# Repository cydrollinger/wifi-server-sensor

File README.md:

<a href="https://elec-real.com/case-studies/wifi-server-sensor/"></img></a>

>Electronic Realization L.L.C.								   
>Design: Wifi communication web server 		   
>Engineer: Cy Drollinger								   
>Date: 8/15												           
>Email: cy@elec-real.com
>Website: https://elec-real.com								   
>Address: 2023 Stadium Dr Suite 2B #210 Bozeman, MT 59715				   
>Phone: 406-539-8117	

**NOTE:**
 This design has been tested and functions as specified. The design is provided gratis, so, please 
 think critically while utilizing and or redesigning. Open electronic circuitry can be dangerous due 
 to easily shorting circuits which can generate immediate and intense heat resulting in fire. Conversation is
 welcome to improve this design and repository, but, be advised ER is a professional design house and
 monetary compensation is required for additional work toward this design enabling your success.			   

**PURPOSE:**
This is a redesign of a Microchip product, a web server. 

>**File Arcitecture with a terse description**

* FOLDERS:
	* docs		: datasheets 
	* hardware	: eagle cadsoft(v7.7) hardware design files 	
		* eagleup		: 3D files 
		* library		: eagle part files 
		* manufacturing	: files required to produce the design
			* bom	: files created to order the parts	
			* gerber	: files generated to manufacture the board
				* <a href="https://oshpark.com/shared_projects/WaZovepw"></img></a>
			* mount	: 
			
	* firmware
	* flexware
	* software

	* readme.md	: this file

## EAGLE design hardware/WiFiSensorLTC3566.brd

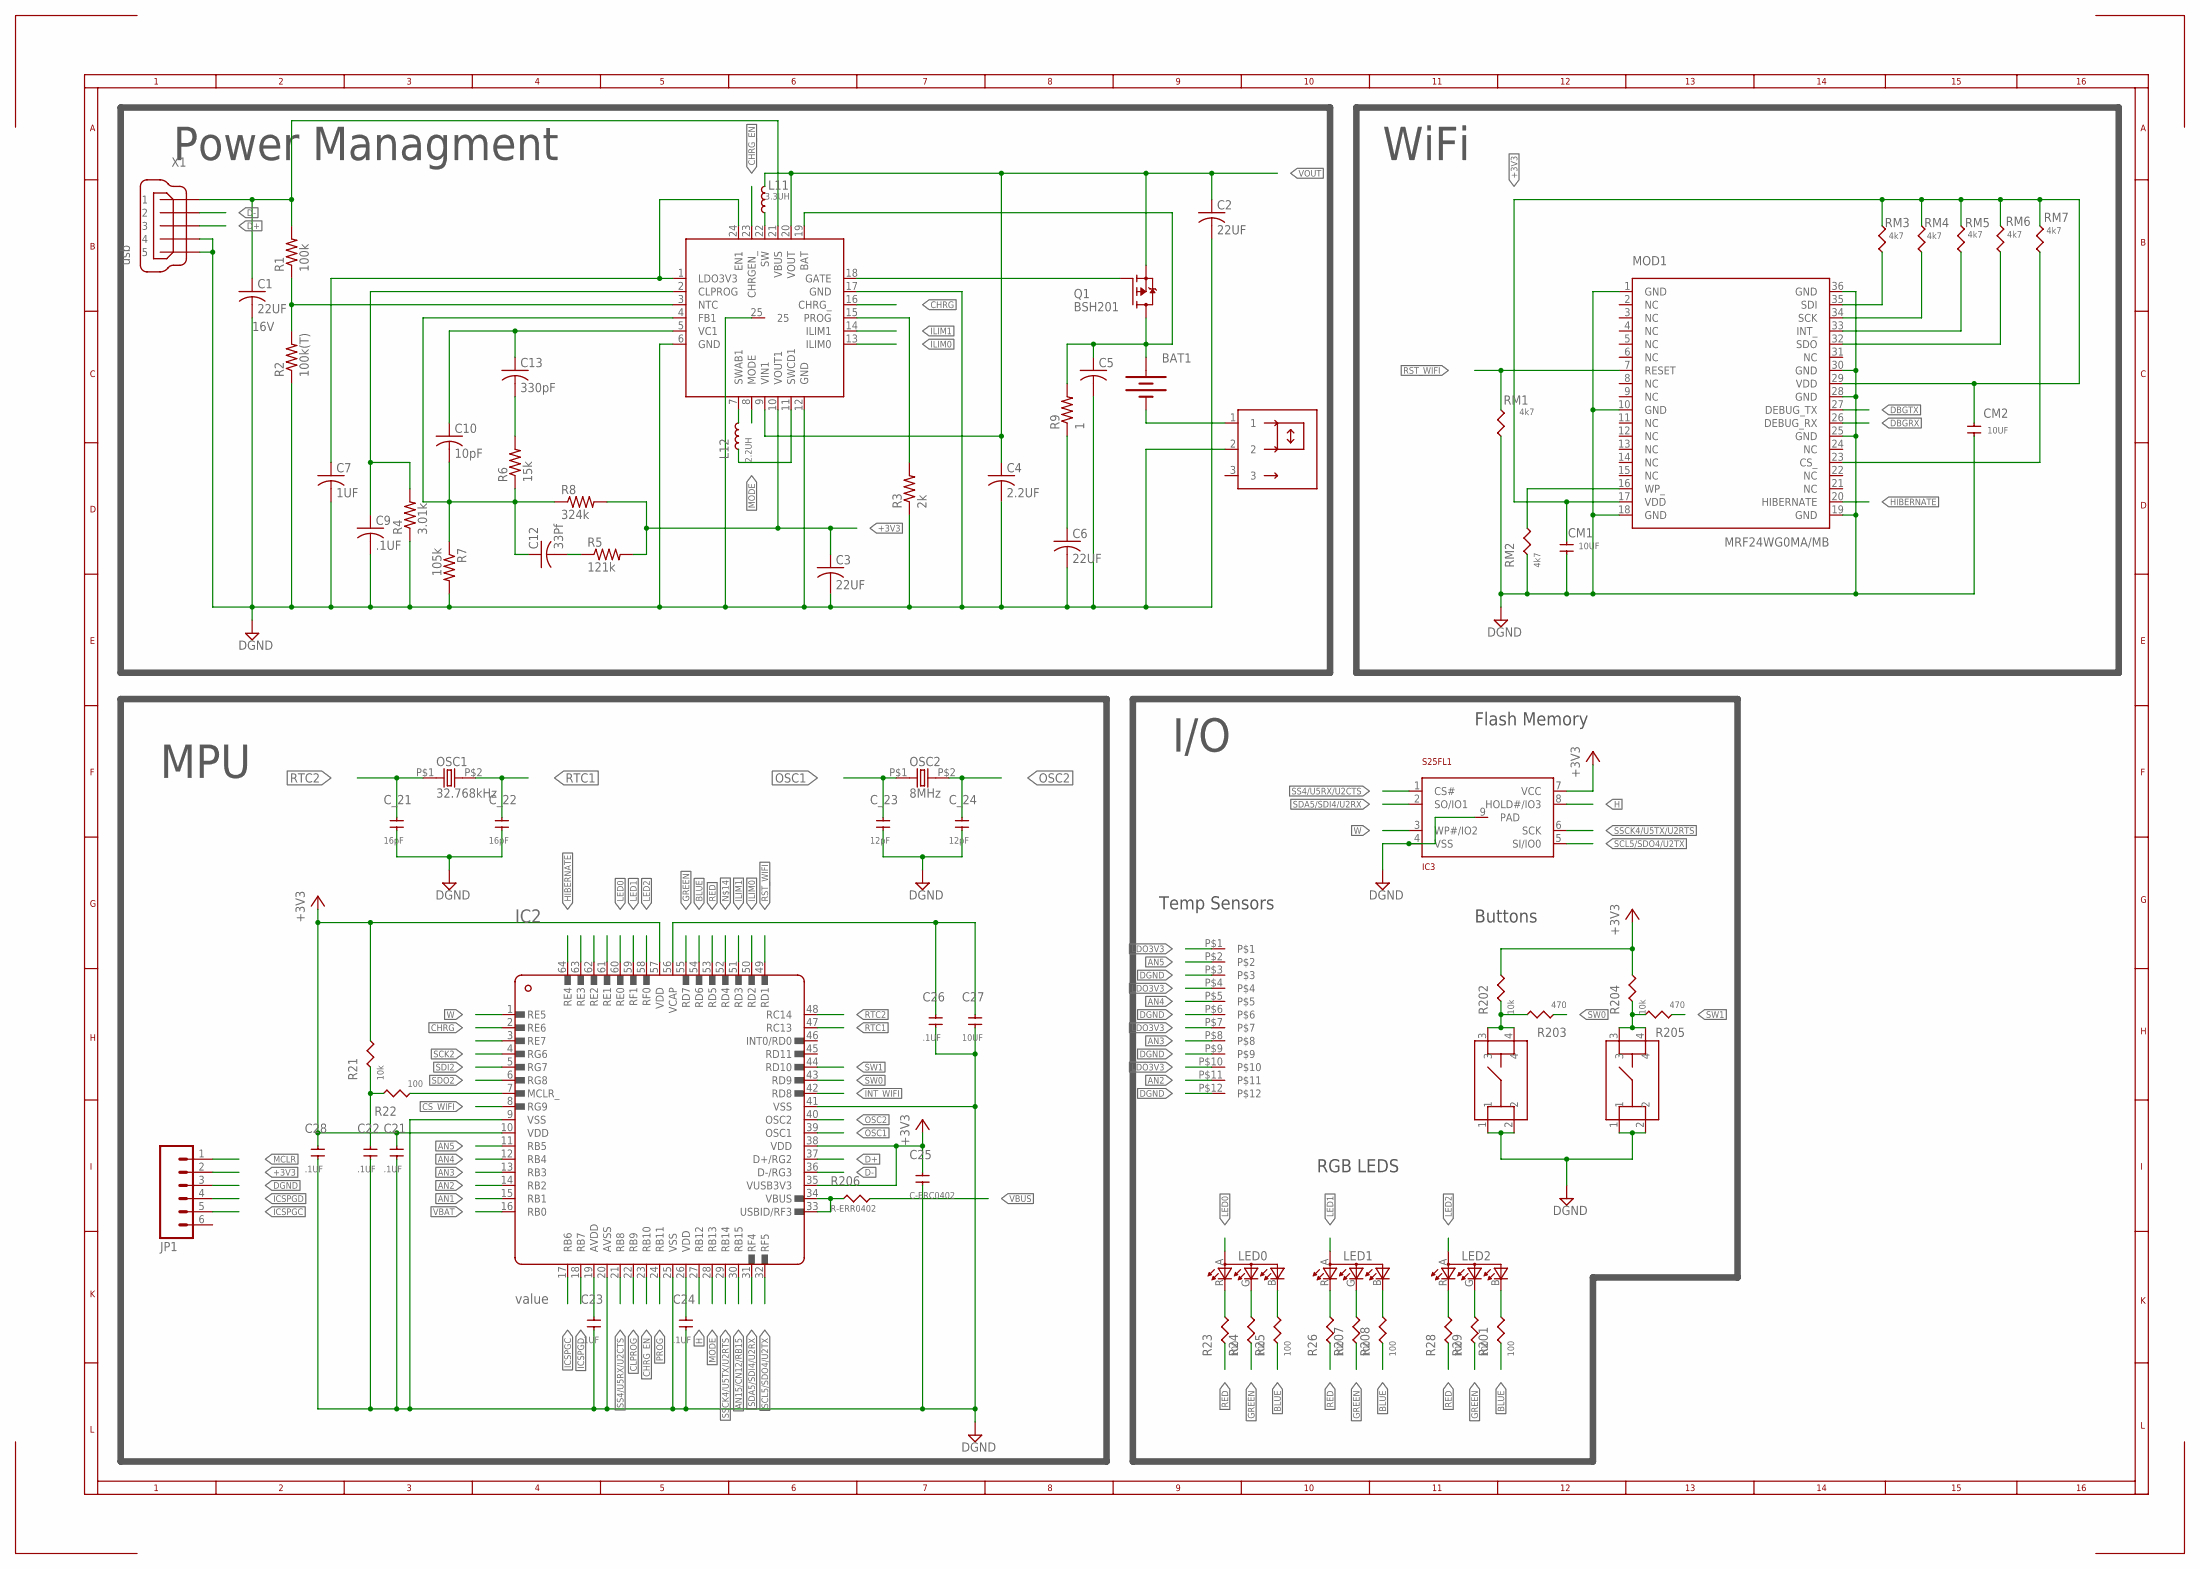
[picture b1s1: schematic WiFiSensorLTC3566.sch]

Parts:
BAT1: BATTERY245PTH; BATTCON_245MM_PTH
C1: 22UF; C0805; VOLTAGECOEFFECIENT 16V
C2, C3, C6: 22UF; C0805
C4: 2.2UF; C0805
C5: C-USC0402; C0402
C7: 1UF; C0805
C9, C21, C22, C23, C24, C26, C28: .1UF; C0402
C10: 10pF; C0402
C12: 33Pf; C0402
C13: 330pF; C0402
C25: C-ERC0402; C0402
C27: 10UF; C0805
CM1, CM2: 10UF; C0805
C_21, C_22: 16pF; C0402
C_23, C_24: 12pF; C0402
IC1: LTC3566-2; QFN24-4X4
IC2: PICMX32695F512H; TQFP64
IC3: S25FL1; 8WSON
JP1: M06LOCK; 1X06_LOCK
JP2: 12_127; 12-127
L11: 3.3UH; VLCF5020
L12: 2.2UH; VLCF5020
LED0, LED1, LED2: 1X1RGB; 1X1
MOD1: MRF24WG0MA/MB; MRF24
OSC1: 32.768kHz; ECX39; DIGIPART XC1658CT-ND
OSC2: 8MHz; CX532; DIGIPART XC1658CT-ND
Q1: BSH201; SOT23
R1: 100k; R0402
R2: 100k(T); R0402
R3: 2k; R0402
R4: 3.01k; R0402
R5: 121k; R0402
R6: 15k; R0402
R7: 105k; R0402
R8: 324k; R0402
R9: 1; R0402
R21, R202, R204: 10k; R0402
R22, R23, R24, R25, R26, R28, R29, R201, R207, R208: 100; R0402
R203, R205: 470; R0402
R206: R-ERR0402; R0402
RM1, RM2, RM3, RM4, RM5, RM6, RM7: 4k7; R0402
SW0, SW1: ADTS; 4X5
SW2: C&K_JS; SAQN
X1: usb; UX60A-MB-5ST

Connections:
+3V3: C3.1, C21.2, C24.2, C25.2, C28.2, CM1.2, CM2.2, IC1.10 (VOUT1), IC2.10 (VDD), IC2.26 (VDD), IC2.35 (VUSB3V3), IC2.38 (VDD), IC2.57 (VDD), IC3.7 (VCC), JP1.2, MOD1.17 (VDD), MOD1.29 (VDD), R5.2, R8.2, R21.2, R202.2, R204.2, RM3.2, RM4.2, RM5.2, RM6.2, RM7.2
AN1: IC2.15 (RB1)
AN2: IC2.14 (RB2), JP2.P$11
AN3: IC2.13 (RB3), JP2.P$8
AN4: IC2.12 (RB4), JP2.P$5
AN5: IC2.11 (RB5), JP2.P$2
AN15/CN12/RB15: IC2.30 (RB15)
BLUE: IC2.54 (RD6), R25.1, R201.1, R208.1
CHRG: IC1.16 (CHRG_), IC2.2 (RE6)
CHRG_EN: IC1.23 (CHRGEN_), IC2.23 (RB10)
CLPROG: C9.1, IC1.2 (CLPROG), IC2.22 (RB9), R4.2
CS_WIFI: IC2.8 (RG9), MOD1.23 (CS_), RM7.1
D+: IC2.37 (D+/RG2), X1.3
D-: IC2.36 (D-/RG3), X1.2
DBGRX: MOD1.26 (DEBUG_RX)
DBGTX: MOD1.27 (DEBUG_TX)
DGND: C1.2, C2.2, C3.2, C4.2, C5.2, C6.2, C7.2, C9.2, C21.1, C22.1, C23.1, C24.1, C25.1, C26.1, C27.1, C28.1, CM1.1, CM2.1, C_21.1, C_22.1, C_23.1, C_24.1, IC1.6 (GND), IC1.12 (GND), IC1.17 (GND), IC1.25, IC2.9 (VSS), IC2.20 (AVSS), IC2.25 (VSS), IC2.41 (VSS), IC3.4 (VSS), IC3.9 (PAD), JP1.3, JP2.P$3, JP2.P$6, JP2.P$9, JP2.P$12, MOD1.1 (GND), MOD1.10 (GND), MOD1.18 (GND), MOD1.19 (GND), MOD1.25 (GND), MOD1.28 (GND), MOD1.30 (GND), MOD1.36 (GND), R2.1, R3.1, R4.1, R7.2, RM1.1, RM2.1, SW0.1, SW0.2, SW1.1, SW1.2, SW2.2, X1.4, X1.5
GREEN: IC2.55 (RD7), R24.1, R29.1, R207.1
H: IC2.27 (RB12), IC3.8 (HOLD#/IO3)
HIBERNATE: IC2.64 (RE4), MOD1.20 (HIBERNATE)
ICSPGC: IC2.17 (RB6), JP1.5
ICSPGD: IC2.18 (RB7), JP1.4
ILIM0: IC1.13 (ILIM0), IC2.50 (RD2)
ILIM1: IC1.14 (ILIM1), IC2.51 (RD3)
INT_WIFI: IC2.42 (RD8), MOD1.33 (INT_), RM5.1
LDO3V3: C7.1, C23.2, IC1.1 (LDO3V3), IC1.24 (EN1), IC2.19 (AVDD), JP2.P$1, JP2.P$4, JP2.P$7, JP2.P$10
LED0: IC2.60 (RE0), LED0.A (A2)
LED1: IC2.59 (RF1), LED1.A (A2)
LED2: IC2.58 (RF0), LED2.A (A2)
MCLR: C22.2, JP1.1, R21.1, R22.2
MODE: IC1.8 (MODE), IC2.28 (RB13)
unnamed: IC1.22 (SW), L11.P$1
unnamed: C6.1, R9.1
unnamed: IC1.7 (SWAB1), L12.P$2
unnamed: IC1.11 (SWCD1), L12.P$1
unnamed: C12.2, R5.1
unnamed: IC1.3 (NTC), R1.1, R2.2
unnamed: C13.2, R6.2
unnamed: C10.1, C13.1, IC1.5 (VC1)
unnamed: C10.2, C12.1, IC1.4 (FB1), R6.1, R7.1, R8.1
unnamed: BAT1.2 (-), SW2.1
unnamed: IC1.18 (GATE), Q1.1 (G)
unnamed: IC2.33 (USBID/RF3), IC2.34 (VBUS), R206.1
unnamed: IC2.7 (MCLR_), R22.1
unnamed: R202.1, R203.2, SW0.3, SW0.4
unnamed: C26.2, C27.2, IC2.56 (VCAP)
unnamed: R204.1, R205.2, SW1.3, SW1.4
unnamed: LED0.R (CRED), R23.2
unnamed: LED0.G (CBLUE), R24.2
unnamed: MOD1.16 (WP_), RM2.2
unnamed: LED0.B (CGREEN), R25.2
unnamed: LED1.R (CRED), R26.2
unnamed: LED1.G (CBLUE), R207.2
unnamed: LED1.B (CGREEN), R208.2
unnamed: LED2.R (CRED), R28.2
unnamed: LED2.G (CBLUE), R29.2
unnamed: LED2.B (CGREEN), R201.2
OSC1: C_23.2, IC2.39 (OSC1), OSC2.P$1 (1)
OSC2: C_24.2, IC2.40 (OSC2), OSC2.P$2 (2)
PROG: IC1.15 (PROG), IC2.24 (RB11), R3.2
RED: IC2.53 (RD5), R23.1, R26.1, R28.1
RST_WIFI: IC2.49 (RD1), MOD1.7 (RESET), RM1.2
RTC1: C_22.2, IC2.47 (RC13), OSC1.P$2 (2)
RTC2: C_21.2, IC2.48 (RC14), OSC1.P$1 (1)
SCK2: IC2.4 (RG6), MOD1.34 (SCK), RM4.1
SCL5/SDO4/U2TX: IC2.32 (RF5), IC3.5 (SI/IO0)
SDA5/SDI4/U2RX: IC2.31 (RF4), IC3.2 (SO/IO1)
SDI2: IC2.5 (RG7), MOD1.32 (SDO), RM6.1
SDO2: IC2.6 (RG8), MOD1.35 (SDI), RM3.1
SS4/U5RX/U2CTS: IC2.21 (RB8), IC3.1 (CS#)
SSCK4/U5TX/U2RTS: IC2.29 (RB14), IC3.6 (SCK)
SW0: IC2.43 (RD9), R203.1
SW1: IC2.44 (RD10), R205.1
VBAT: BAT1.3 (+), C5.1, IC1.19 (BAT), IC2.16 (RB0), Q1.3 (D), R9.2
VBUS: C1.1, IC1.21 (VBUS), R1.2, R206.2, X1.1
VOUT: C2.1, C4.1, IC1.9 (VIN1), IC1.20 (VOUT), L11.P$2, Q1.2 (S)
W: IC2.1 (RE5), IC3.3 (WP#/IO2)

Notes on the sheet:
WiFi
Power Managment
MPU
I/O
Temp Sensors
Buttons
RGB LEDS
Flash Memory

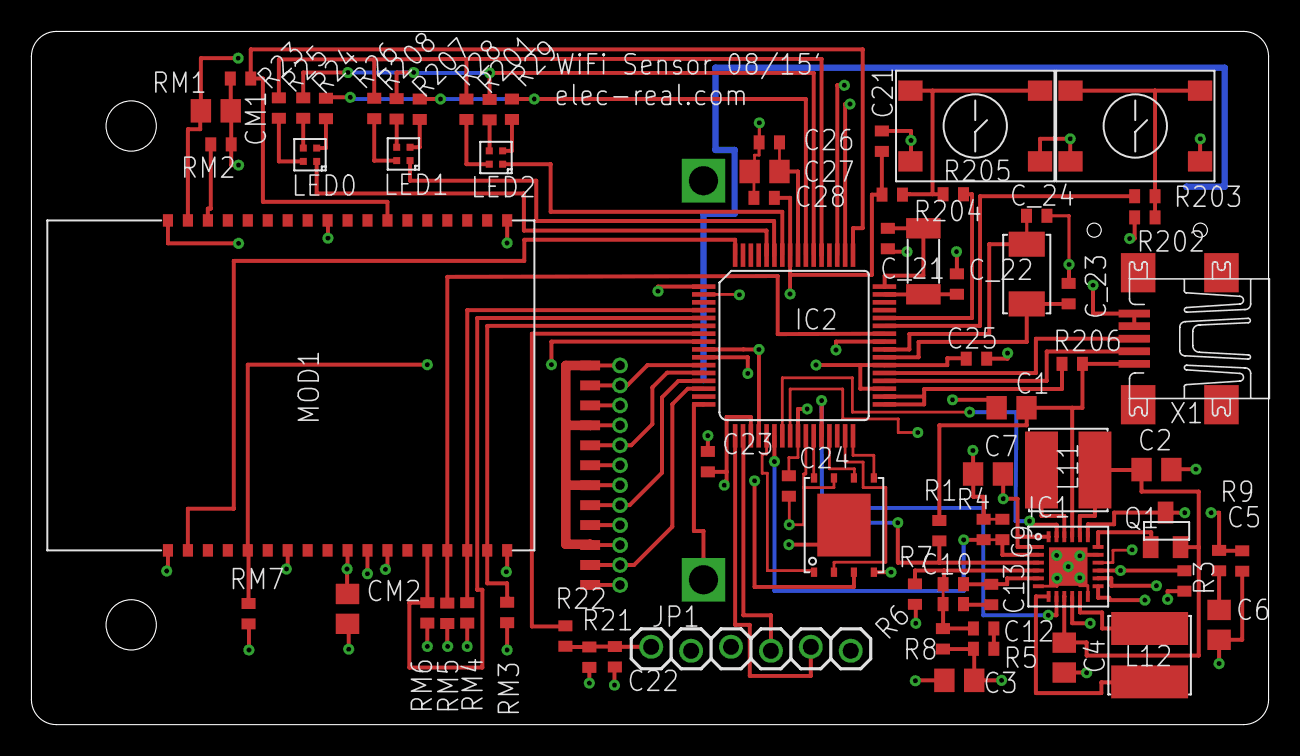
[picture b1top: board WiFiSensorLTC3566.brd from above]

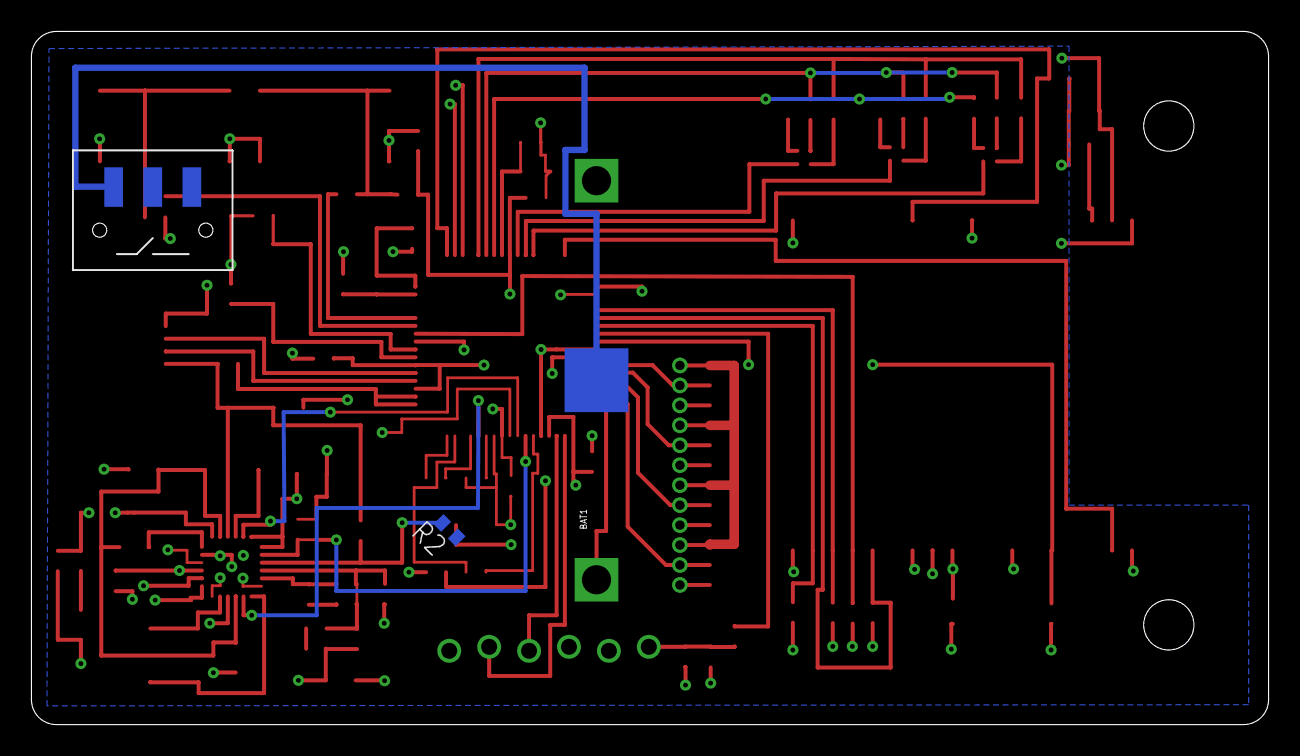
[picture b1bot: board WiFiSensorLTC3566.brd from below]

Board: 4 copper layers, 78.7 x 44.1 mm, 76 parts (3 on the bottom side), 73 nets.

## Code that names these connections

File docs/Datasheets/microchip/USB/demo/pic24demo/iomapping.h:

/************************************************************************
*                                                                       *
* This redefines I/O mapping for each device family                     *
*                                                                       *
*************************************************************************
* Company:             Microchip Technology, Inc.                       *
*                                                                       *
* Software License Agreement                                            *
*                                                                       *
* The software supplied herewith by Microchip Technology Incorporated   *
* (the "Company") for its PICmicro® Microcontroller is intended and     *
* supplied to you, the Company's customer, for use solely and           *
* exclusively on Microchip PICmicro Microcontroller products. The       *
* software is owned by the Company and/or its supplier, and is          *
* protected under applicable copyright laws. All rights are reserved.   *
* Any use in violation of the foregoing restrictions may subject the    *
* user to criminal sanctions under applicable laws, as well as to       *
* civil liability for the breach of the terms and conditions of this    *
* license.                                                              *
*                                                                       *
* THIS SOFTWARE IS PROVIDED IN AN "AS IS" CONDITION. NO WARRANTIES,     *
* WHETHER EXPRESS, IMPLIED OR STATUTORY, INCLUDING, BUT NOT LIMITED     *
* TO, IMPLIED WARRANTIES OF MERCHANTABILITY AND FITNESS FOR A           *
* PARTICULAR PURPOSE APPLY TO THIS SOFTWARE. THE COMPANY SHALL NOT,     *
* IN ANY CIRCUMSTANCES, BE LIABLE FOR SPECIAL, INCIDENTAL OR            *
* CONSEQUENTIAL DAMAGES, FOR ANY REASON WHATSOEVER.                     *
************************************************************************/

#ifndef IOMAPPING_H	
#define IOMAPPING_H

extern void ioMap();
extern void unlock();
extern void lockIO();

    #if defined(__PIC24FJ64GA004__)
        //ADC input mapping
        #define AN_VOLT_PIN  	AD1PCFGbits.PCFG7			//voltage input on AN7
        #define ADC_VOLT_CHAN	7
        
        #define AN_TEMP_PIN	 	AD1PCFGbits.PCFG6 			//temp input on AN6
        #define ADC_TEMP_CHAN	6
                
        //Push Button I/O Mapping
        #define BUTTON1_IO		PORTAbits.RA10
        #define BUTTON2_IO		PORTAbits.RA9
        #define BUTTON3_IO		PORTCbits.RC6
        #define BUTTON4_IO		PORTAbits.RA7
        
        #define BUTTON1_TRIS	TRISAbits.TRISA10
        #define BUTTON2_TRIS	TRISAbits.TRISA9
        #define BUTTON3_TRIS	TRISCbits.TRISC6
        #define BUTTON4_TRIS	TRISAbits.TRISA7
        
        
        //LED I/O Mapping
        #define LED0_IO			LATAbits.LATA10
        #define LED1_IO			LATAbits.LATA7
        #define LED2_IO			LATBbits.LATB8
        #define LED3_IO			LATBbits.LATB9
        #define LED4_IO			LATAbits.LATA9
        #define LED5_IO			LATAbits.LATA8
        #define LED6_IO			LATBbits.LATB12
        #define LED7_IO			LATCbits.LATC6
        
        #define LED0_TRIS		TRISAbits.TRISA10
        #define LED1_TRIS		TRISAbits.TRISA7			
        #define LED2_TRIS		TRISBbits.TRISB8
        #define LED3_TRIS		TRISBbits.TRISB9
        #define LED4_TRIS		TRISAbits.TRISA9
        #define LED5_TRIS		TRISAbits.TRISA8
        #define LED6_TRIS		TRISBbits.TRISB12
        #define LED7_TRIS		TRISCbits.TRISC6
        
        
        //SPI I/O Mapping
        #define PPS_SPI_SS_IO		LATAbits.LATA8
        #define PPS_SPI_SS_TRIS	    TRISAbits.TRISA8
        #define PPS_SPI_SCK_TRIS	TRISCbits.TRISC8
        #define PPS_SPI_SDI_TRIS	TRISCbits.TRISC4
        #define PPS_SPI_SDO_TRIS	TRISCbits.TRISC5
        
        
        //UART I/O Mapping
        #define PPS_UART2_TX_TRIS		TRISCbits.TRISC9
        #define PPS_UART2_RX_TRIS		TRISCbits.TRISC3
        
        //PPS Outputs
        #define NULL_IO		0
        #define C1OUT_IO	1
        #define C2OUT_IO	2
        #define U1TX_IO		3
        #define U1RTS_IO	4
        #define U2TX_IO		5
        #define U2RTS_IO	6
        #define SDO1_IO		7
        #define SCK1OUT_IO	8
        #define SS1OUT_IO	9
        #define SDO2_IO		10
        #define SCK2OUT_IO	11
        #define SS2OUT_IO	12
        #define OC1_IO		18
        #define OC2_IO		19
        #define OC3_IO		20
        #define OC4_IO		21
        #define OC5_IO		22
    #endif //__PIC24FJ64GA004__

    #if defined(__PIC24FJ256GB110__) || defined(__PIC24FJ256GA110__)
        //ADC input mapping
        #define AN_VOLT_PIN  	AD1PCFGbits.PCFG5			//voltage input on AN5
        #define ADC_VOLT_CHAN	5
        
        #define AN_TEMP_PIN	 	AD1PCFGbits.PCFG4 			//temp input on AN4
        #define ADC_TEMP_CHAN	4
        
        
        //Push Button I/O Mapping
        #define BUTTON1_IO		PORTDbits.RD6
        #define BUTTON2_IO		PORTDbits.RD7
        #define BUTTON3_IO		PORTAbits.RA7
        #define BUTTON4_IO		PORTDbits.RD13
        
        #define BUTTON1_TRIS	TRISDbits.TRISD6
        #define BUTTON2_TRIS	TRISDbits.TRISD7
        #define BUTTON3_TRIS	TRISAbits.TRISA7
        #define BUTTON4_TRIS	TRISDbits.TRISD13
        
        
        //LED I/O Mapping
        #define LED0_IO			LATAbits.LATA0
        #define LED1_IO			LATAbits.LATA1
        #define LED2_IO			LATAbits.LATA2
        #define LED3_IO			LATAbits.LATA3
        #define LED4_IO			LATAbits.LATA4
        #define LED5_IO			LATAbits.LATA5
        #define LED6_IO			LATAbits.LATA6
        #define LED7_IO			LATAbits.LATA7
        
        #define LED0_TRIS		TRISAbits.TRISA0
        #define LED1_TRIS		TRISAbits.TRISA1			
        #define LED2_TRIS		TRISAbits.TRISA2
        #define LED3_TRIS		TRISAbits.TRISA3
        #define LED4_TRIS		TRISAbits.TRISA4
        #define LED5_TRIS		TRISAbits.TRISA5
        #define LED6_TRIS		TRISAbits.TRISA6
        #define LED7_TRIS		TRISAbits.TRISA7
        
        
        //SPI I/O Mapping
        #if defined(__PIC24FJ256GA110__)
            #define PPS_SPI_SS_IO		LATDbits.LATD12
            #define PPS_SPI_SS_TRIS	    TRISDbits.TRISD12
        #else       //__PIC24FJ256GB110__
            #define PPS_SPI_SS_IO		LATGbits.LATG0
            #define PPS_SPI_SS_TRIS	    TRISGbits.TRISG0
        #endif
        #define PPS_SPI_SCK_TRIS	TRISGbits.TRISG6
        #define PPS_SPI_SDI_TRIS	TRISGbits.TRISG7
        #define PPS_SPI_SDO_TRIS	TRISGbits.TRISG8
        
        
        //UART I/O Mapping
        #define PPS_UART2_TX_TRIS		TRISFbits.TRISF5
        #define PPS_UART2_RX_TRIS		TRISFbits.TRISF4
        
        //PPS Outputs
        #define NULL_IO		0
        #define C1OUT_IO	1
        #define C2OUT_IO	2
        #define U1TX_IO		3
        #define U1RTS_IO	4
        #define U2TX_IO		5
        #define U2RTS_IO	6
        #define SDO1_IO		7
        #define SCK1OUT_IO	8
        #define SS1OUT_IO	9
        #define SDO2_IO		10
        #define SCK2OUT_IO	11
        #define SS2OUT_IO	12
        #define OC1_IO		18
        #define OC2_IO		19
        #define OC3_IO		20
        #define OC4_IO		21
        #define OC5_IO		22
        #define OC6_IO      23
        #define OC7_IO      24
        #define OC8_IO      25
        #define U3TX_IO     28
        #define U3RTS_IO    29
        #define U4TX_IO     30
        #define U4RTS_IO    31
        #define SDO3_IO     32
        #define SCK3OUT_IO  33
        #define SS3OUT_IO   34
        #define OC9_IO      35
    #endif //__PIC24FJ256GB110__ || __PIC24FJ256GA110__
#endif

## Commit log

2019-04-19 first commit 4/18/19
2019-04-26 first commit 4/26/19
2019-04-27 first commit 4/27/19
2019-04-30 first commit 4/30/19
